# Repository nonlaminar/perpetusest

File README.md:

# perpetusest
For the wandering writer, seeking a keyboard and and space

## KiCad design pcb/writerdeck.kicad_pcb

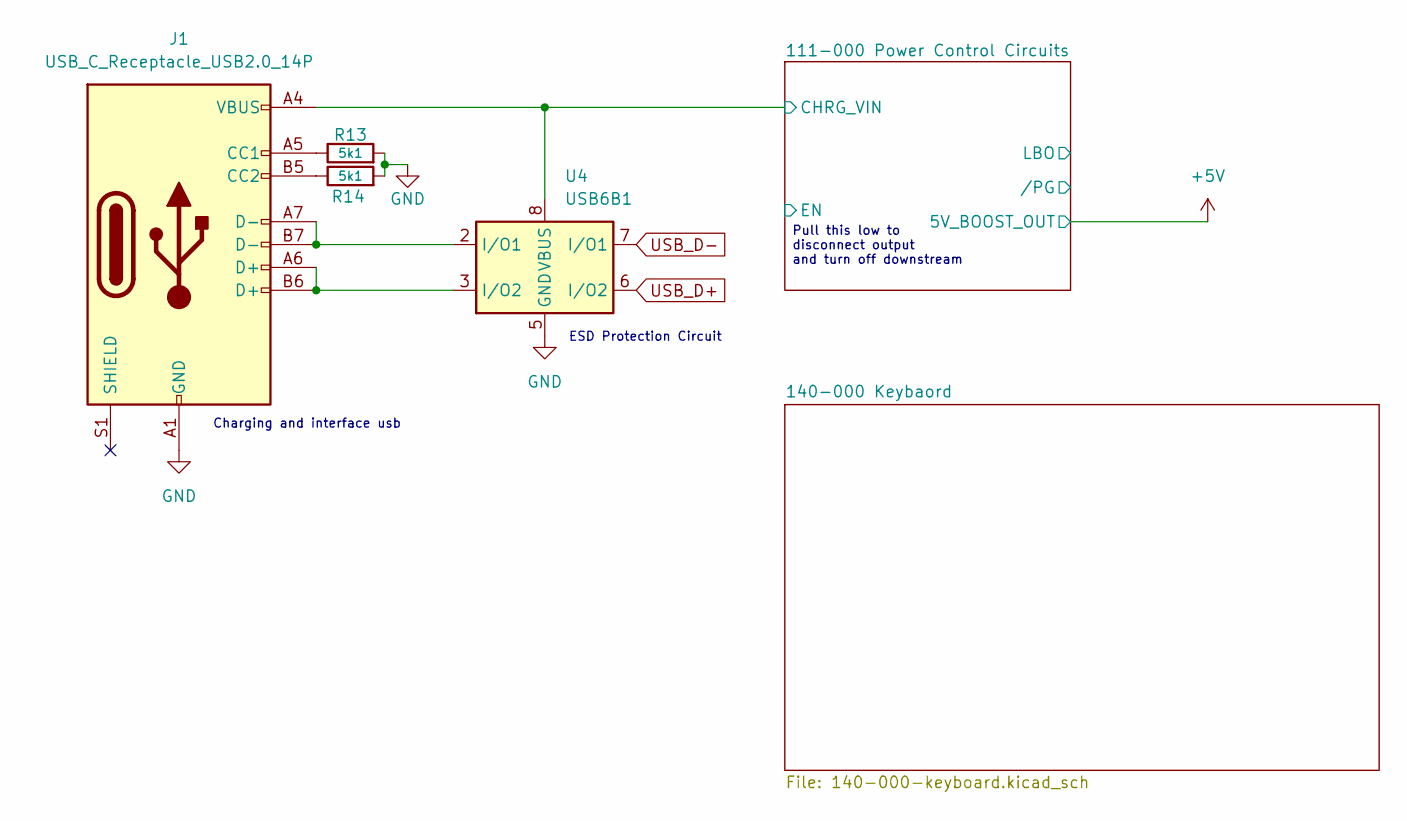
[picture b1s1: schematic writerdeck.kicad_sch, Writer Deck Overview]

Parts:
J1: USB_C_Receptacle_USB2.0_14P
R13, R14: 5k1; R_0402_1005Metric
U4: USB6B1; SOIC-8_3.9x4.9mm_P1.27mm

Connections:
/111-000 Power Control Circuits/CHRG_VIN: J1.A4 (VBUS), J1.A9 (VBUS), J1.B4 (VBUS), J1.B9 (VBUS), U4.1 (VBUS), U4.8 (VBUS); also elsewhere on the board
GND: J1.A1 (GND), J1.A12 (GND), J1.B1 (GND), J1.B12 (GND), R13.2, R14.2, U4.4 (GND), U4.5 (GND); also elsewhere on the board
unnamed: J1.A5 (CC1), R13.1
unnamed: J1.B5 (CC2), R14.1
unnamed: J1.A6 (D+), J1.B6 (D+), U4.3 (I/O2)
unnamed: J1.A7 (D-), J1.B7 (D-), U4.2 (I/O1)
USB_D+: U4.6 (I/O2)
USB_D-: U4.7 (I/O1)

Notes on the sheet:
Charging and interface usb
ESD Protection Circuit
Pull this low to disconnect output and turn off downstream

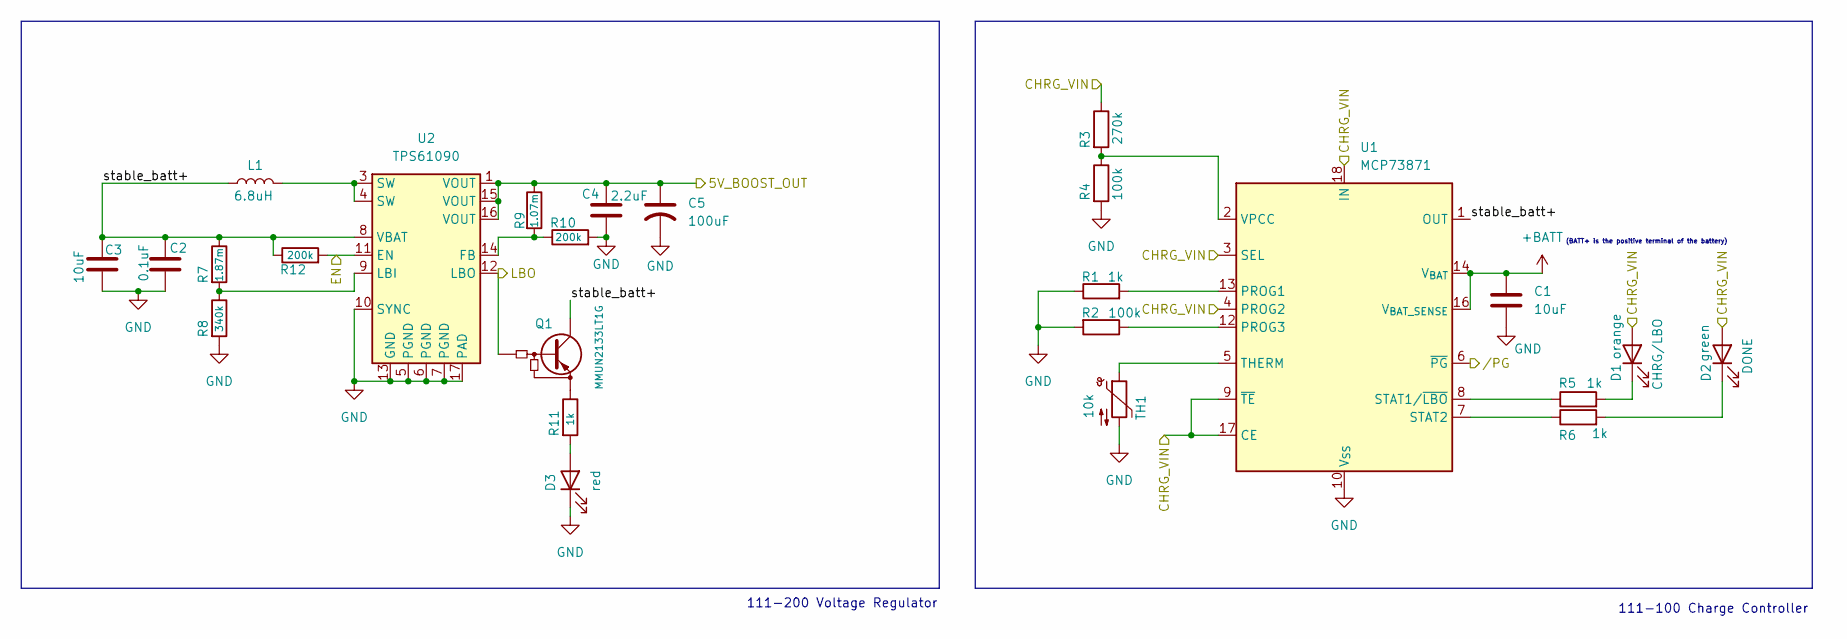
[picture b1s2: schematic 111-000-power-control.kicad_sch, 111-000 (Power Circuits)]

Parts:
C1, C3: 10uF; C_0402_1005Metric
C2: 0.1uF; C_0402_1005Metric
C4: 2.2uF; C_0402_1005Metric
C5: 100uF; C_0402_1005Metric
D1: orange
D2: green
D3: red
L1: 6.8uH
Q1: MMUN2133LT1G
R1, R5, R6, R11: 1k; R_0402_1005Metric
R2, R4: 100k; R_0402_1005Metric
R3: 270k; R_0402_1005Metric
R7: 1.87m; R_0402_1005Metric
R8: 340k; R_0402_1005Metric
R9: 1.07m; R_0402_1005Metric
R10, R12: 200k; R_0402_1005Metric
TH1: 10k; R_0402_1005Metric
U1: MCP73871; QFN-20-1EP_4x4mm_P0.5mm_EP2.5x2.5mm
U2: TPS61090; Texas_RSA_VQFN-16-1EP_4x4mm_P0.65mm_EP2.7x2.7mm_ThermalVias

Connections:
+5V: C4.1, C5.1, R9.1, U2.1 (VOUT), U2.15 (VOUT), U2.16 (VOUT); also elsewhere on the board
+BATT: C1.1, U1.14 (V_{BAT}), U1.15 (V_{BAT}), U1.16 (V_{BAT_SENSE})
/111-000 Power Control Circuits/CHRG_VIN: D1.2 (A), D2.2 (A), R3.1, U1.3 (SEL), U1.4 (PROG2), U1.9 (~TE), U1.17 (CE), U1.18 (IN), U1.19 (IN); also elsewhere on the board
/111-000 Power Control Circuits/EN: R12.2, U2.11 (EN)
/111-000 Power Control Circuits/LBO: Q1.B, U2.12 (LBO)
/111-000 Power Control Circuits/stable_batt+: C2.1, C3.1, L1.1, Q1.C, R7.1, R12.1, U1.1 (OUT), U1.20 (OUT), U2.8 (VBAT)
/111-000 Power Control Circuits//PG: U1.6 (~PG)
GND: C1.2, C2.2, C3.2, C4.2, C5.2, D3.1 (K), R1.1, R2.2, R4.2, R8.2, R10.2, TH1.2, U1.10 (V_{SS}), U1.11 (V_{SS}), U1.21 (V_{SS}), U2.5 (PGND), U2.6 (PGND), U2.7 (PGND), U2.10 (SYNC), U2.13 (GND), U2.17 (PAD); also elsewhere on the board
unnamed: D1.1 (K), R5.2
unnamed: D2.1 (K), R6.2
unnamed: D3.2 (A), R11.2
unnamed: L1.2, U2.3 (SW), U2.4 (SW)
unnamed: Q1.E, R11.1
unnamed: R1.2, U1.13 (PROG1)
unnamed: R2.1, U1.12 (PROG3)
unnamed: R5.1, U1.8 (STAT1/~LBO)
unnamed: R6.1, U1.7 (STAT2)
unnamed: TH1.1, U1.5 (THERM)
unnamed: R3.2, R4.1, U1.2 (VPCC)
unnamed: R9.2, R10.1, U2.14 (FB)
unnamed: R7.2, R8.1, U2.9 (LBI)

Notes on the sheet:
(BATT+ is the positive terminal of the battery)
111-100 Charge Controller
111-200 Voltage Regulator

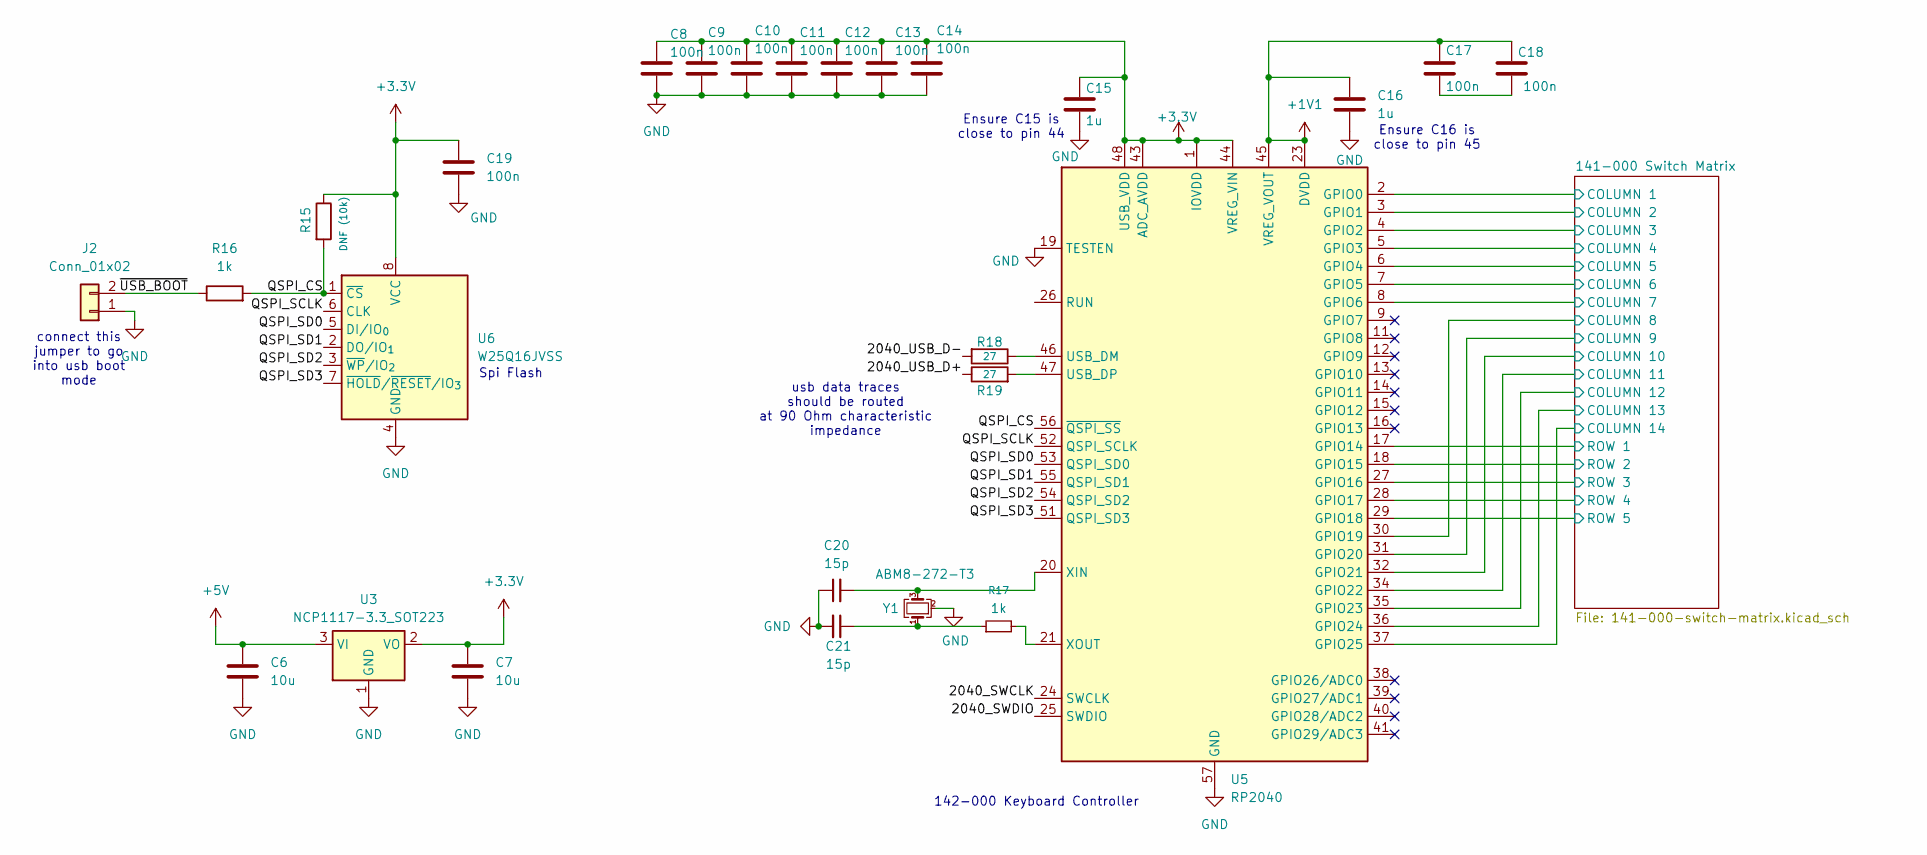
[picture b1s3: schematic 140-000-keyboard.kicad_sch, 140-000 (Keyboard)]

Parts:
C6, C7: 10u; C_0402_1005Metric
C8, C9, C10, C11, C12, C13, C14, C17, C18, C19: 100n; C_0402_1005Metric
C15, C16: 1u; C_0402_1005Metric
C20, C21: 15p; C_0402_1005Metric
J2: Conn_01x02
R15: DNF (10k); R_0402_1005Metric
R16, R17: 1k; R_0402_1005Metric
R18, R19: 27; R_0402_1005Metric
U3: NCP1117-3.3_SOT223; SOT-223-3_TabPin2
U5: RP2040; QFN-56-1EP_7x7mm_P0.4mm_EP3.2x3.2mm
U6: W25Q16JVSS; SOIC-8_5.3x5.3mm_P1.27mm
Y1: ABM8-272-T3; ABM8-272-T3_ABR

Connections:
+1V1: C16.1, C17.1, C18.1, U5.23 (DVDD), U5.45 (VREG_VOUT), U5.50 (DVDD)
+3.3V: C7.1, C8.1, C9.1, C10.1, C11.1, C12.1, C13.1, C14.1, C15.1, C19.1, R15.1, U3.2 (VO), U5.1 (IOVDD), U5.10 (IOVDD), U5.22 (IOVDD), U5.33 (IOVDD), U5.42 (IOVDD), U5.43 (ADC_AVDD), U5.44 (VREG_VIN), U5.48 (USB_VDD), U5.49 (IOVDD), U6.8 (VCC)
+5V: C6.1, U3.3 (VI); also elsewhere on the board
/140-000 Keybaord/141-000 Switch Matrix/COLUMN 1: U5.2 (GPIO0); also elsewhere on the board
/140-000 Keybaord/141-000 Switch Matrix/COLUMN 2: U5.3 (GPIO1); also elsewhere on the board
/140-000 Keybaord/141-000 Switch Matrix/COLUMN 3: U5.4 (GPIO2); also elsewhere on the board
/140-000 Keybaord/141-000 Switch Matrix/COLUMN 4: U5.5 (GPIO3); also elsewhere on the board
/140-000 Keybaord/141-000 Switch Matrix/COLUMN 5: U5.6 (GPIO4); also elsewhere on the board
/140-000 Keybaord/141-000 Switch Matrix/COLUMN 6: U5.7 (GPIO5); also elsewhere on the board
/140-000 Keybaord/141-000 Switch Matrix/COLUMN 7: U5.8 (GPIO6); also elsewhere on the board
/140-000 Keybaord/141-000 Switch Matrix/COLUMN 8: U5.30 (GPIO19); also elsewhere on the board
/140-000 Keybaord/141-000 Switch Matrix/COLUMN 9: U5.31 (GPIO20); also elsewhere on the board
/140-000 Keybaord/141-000 Switch Matrix/COLUMN 10: U5.32 (GPIO21); also elsewhere on the board
/140-000 Keybaord/141-000 Switch Matrix/COLUMN 11: U5.34 (GPIO22); also elsewhere on the board
/140-000 Keybaord/141-000 Switch Matrix/COLUMN 12: U5.35 (GPIO23); also elsewhere on the board
/140-000 Keybaord/141-000 Switch Matrix/COLUMN 13: U5.36 (GPIO24); also elsewhere on the board
/140-000 Keybaord/141-000 Switch Matrix/COLUMN 14: U5.37 (GPIO25); also elsewhere on the board
/140-000 Keybaord/141-000 Switch Matrix/ROW 1: U5.17 (GPIO14); also elsewhere on the board
/140-000 Keybaord/141-000 Switch Matrix/ROW 2: U5.18 (GPIO15); also elsewhere on the board
/140-000 Keybaord/141-000 Switch Matrix/ROW 3: U5.27 (GPIO16); also elsewhere on the board
/140-000 Keybaord/141-000 Switch Matrix/ROW 4: U5.28 (GPIO17); also elsewhere on the board
/140-000 Keybaord/141-000 Switch Matrix/ROW 5: U5.29 (GPIO18); also elsewhere on the board
/140-000 Keybaord/2040_SWCLK: U5.24 (SWCLK)
/140-000 Keybaord/2040_SWDIO: U5.25 (SWDIO)
/140-000 Keybaord/2040_USB_D+: R19.1
/140-000 Keybaord/2040_USB_D-: R18.2
/140-000 Keybaord/QSPI_CS: R15.2, R16.2, U5.56 (~QSPI_SS), U6.1 (~CS)
/140-000 Keybaord/QSPI_SCLK: U5.52 (QSPI_SCLK), U6.6 (CLK)
/140-000 Keybaord/QSPI_SD0: U5.53 (QSPI_SD0), U6.5 (DI/IO_{0})
/140-000 Keybaord/QSPI_SD1: U5.55 (QSPI_SD1), U6.2 (DO/IO_{1})
/140-000 Keybaord/QSPI_SD2: U5.54 (QSPI_SD2), U6.3 (~WP/IO_{2})
/140-000 Keybaord/QSPI_SD3: U5.51 (QSPI_SD3), U6.7 (~HOLD/~RESET/IO_{3})
/140-000 Keybaord/~USB_BOOT: J2.2, R16.1
GND: C6.2, C7.2, C8.2, C9.2, C10.2, C11.2, C12.2, C13.2, C14.2, C15.2, C16.2, C19.2, C20.1, C21.2, J2.1, U3.1 (GND), U5.19 (TESTEN), U5.57 (GND), U6.4 (GND), Y1.2 (G), Y1.4 (G); also elsewhere on the board
unnamed: C17.2, C18.2
unnamed: C21.1, R17.1, Y1.1
unnamed: R18.1, U5.46 (USB_DM)
unnamed: R19.2, U5.47 (USB_DP)
unnamed: C20.2, U5.20 (XIN), Y1.3
unnamed: R17.2, U5.21 (XOUT)

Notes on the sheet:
usb data traces should be routed at 90 Ohm characteristic impedance
Spi Flash
Ensure C16 is close to pin 45
Ensure C15 is close to pin 44
142-000 Keyboard Controller
connect this jumper to go into usb boot mode

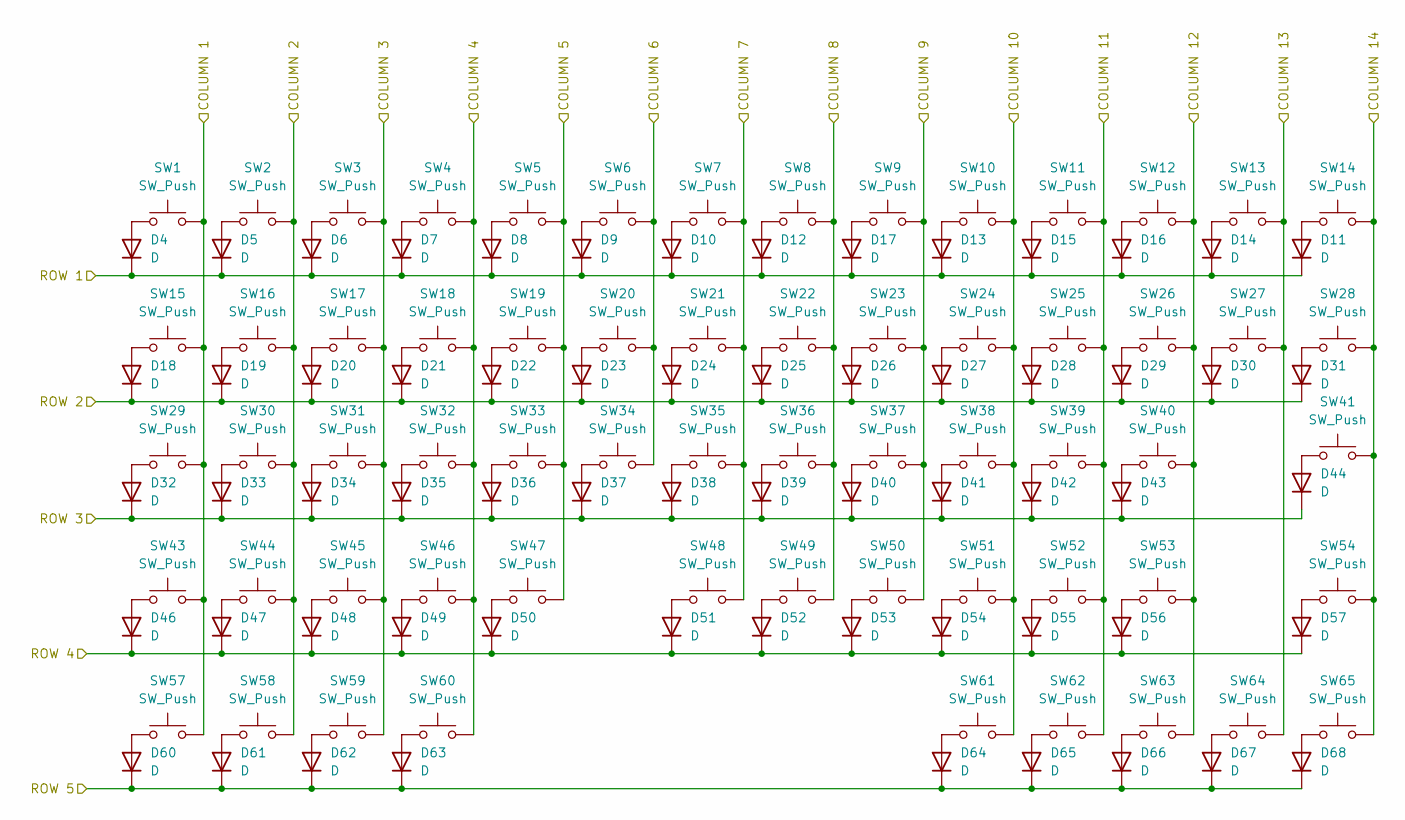
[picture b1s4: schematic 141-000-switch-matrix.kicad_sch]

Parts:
D4, D5, D6, D7, D8, D9, D10, D11, D12, D13, D14, D15, D16, D17, D18, D19, D20, D21, D22, D23, D24, D25, D26, D27, D28, D29, D30, D31, D32, D33, D34, D35, D36, D37, D38, D39, D40, D41, D42, D43, D44, D46, D47, D48, D49, D50, D51, D52, D53, D54, D55, D56, D57, D60, D61, D62, D63, D64, D65, D66, D67, D68: D; D_0402_1005Metric
SW1, SW2, SW3, SW4, SW5, SW6, SW7, SW8, SW9, SW10, SW11, SW12, SW13, SW16, SW17, SW18, SW19, SW20, SW21, SW22, SW23, SW24, SW25, SW26, SW27, SW30, SW31, SW32, SW33, SW34, SW35, SW36, SW37, SW38, SW39, SW40, SW44, SW45, SW46, SW47, SW48, SW49, SW50, SW51, SW52, SW53: SW_Push; SW_Kailh_Choc_V2_1.00u
SW14: SW_Push; SW_Kailh_Choc_V2_2.00u
SW15, SW28, SW65: SW_Push; SW_Kailh_Choc_V2_1.50u
SW29: SW_Push; SW_Kailh_Choc_V2_1.75u
SW41, SW43: SW_Push; SW_Kailh_Choc_V2_2.25u
SW54: SW_Push; SW_Kailh_Choc_V2_2.75u
SW57, SW58, SW59, SW62, SW63, SW64: SW_Push; SW_Kailh_Choc_V2_1.25u
SW60, SW61: SW_Push; SW_Kailh_Choc_V2_3.00u

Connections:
/140-000 Keybaord/141-000 Switch Matrix/COLUMN 1: SW1.2, SW15.2, SW29.2, SW43.2, SW57.2; also elsewhere on the board
/140-000 Keybaord/141-000 Switch Matrix/COLUMN 2: SW2.2, SW16.2, SW30.2, SW44.2, SW58.2; also elsewhere on the board
/140-000 Keybaord/141-000 Switch Matrix/COLUMN 3: SW3.2, SW17.2, SW31.2, SW45.2, SW59.2; also elsewhere on the board
/140-000 Keybaord/141-000 Switch Matrix/COLUMN 4: SW4.2, SW18.2, SW32.2, SW46.2, SW60.2; also elsewhere on the board
/140-000 Keybaord/141-000 Switch Matrix/COLUMN 5: SW5.2, SW19.2, SW33.2, SW47.2; also elsewhere on the board
/140-000 Keybaord/141-000 Switch Matrix/COLUMN 6: SW6.2, SW20.2, SW34.2; also elsewhere on the board
/140-000 Keybaord/141-000 Switch Matrix/COLUMN 7: SW7.2, SW21.2, SW35.2, SW48.2; also elsewhere on the board
/140-000 Keybaord/141-000 Switch Matrix/COLUMN 8: SW8.2, SW22.2, SW36.2, SW49.2; also elsewhere on the board
/140-000 Keybaord/141-000 Switch Matrix/COLUMN 9: SW9.2, SW23.2, SW37.2, SW50.2; also elsewhere on the board
/140-000 Keybaord/141-000 Switch Matrix/COLUMN 10: SW10.2, SW24.2, SW38.2, SW51.2, SW61.2; also elsewhere on the board
/140-000 Keybaord/141-000 Switch Matrix/COLUMN 11: SW11.2, SW25.2, SW39.2, SW52.2, SW62.2; also elsewhere on the board
/140-000 Keybaord/141-000 Switch Matrix/COLUMN 12: SW12.2, SW26.2, SW40.2, SW53.2, SW63.2; also elsewhere on the board
/140-000 Keybaord/141-000 Switch Matrix/COLUMN 13: SW13.2, SW27.2, SW64.2; also elsewhere on the board
/140-000 Keybaord/141-000 Switch Matrix/COLUMN 14: SW14.2, SW28.2, SW41.2, SW54.2, SW65.2; also elsewhere on the board
/140-000 Keybaord/141-000 Switch Matrix/ROW 1: D4.1 (K), D5.1 (K), D6.1 (K), D7.1 (K), D8.1 (K), D9.1 (K), D10.1 (K), D11.1 (K), D12.1 (K), D13.1 (K), D14.1 (K), D15.1 (K), D16.1 (K), D17.1 (K); also elsewhere on the board
/140-000 Keybaord/141-000 Switch Matrix/ROW 2: D18.1 (K), D19.1 (K), D20.1 (K), D21.1 (K), D22.1 (K), D23.1 (K), D24.1 (K), D25.1 (K), D26.1 (K), D27.1 (K), D28.1 (K), D29.1 (K), D30.1 (K), D31.1 (K); also elsewhere on the board
/140-000 Keybaord/141-000 Switch Matrix/ROW 3: D32.1 (K), D33.1 (K), D34.1 (K), D35.1 (K), D36.1 (K), D37.1 (K), D38.1 (K), D39.1 (K), D40.1 (K), D41.1 (K), D42.1 (K), D43.1 (K), D44.1 (K); also elsewhere on the board
/140-000 Keybaord/141-000 Switch Matrix/ROW 4: D46.1 (K), D47.1 (K), D48.1 (K), D49.1 (K), D50.1 (K), D51.1 (K), D52.1 (K), D53.1 (K), D54.1 (K), D55.1 (K), D56.1 (K), D57.1 (K); also elsewhere on the board
/140-000 Keybaord/141-000 Switch Matrix/ROW 5: D60.1 (K), D61.1 (K), D62.1 (K), D63.1 (K), D64.1 (K), D65.1 (K), D66.1 (K), D67.1 (K), D68.1 (K); also elsewhere on the board
unnamed: D4.2 (A), SW1.1
unnamed: D5.2 (A), SW2.1
unnamed: D6.2 (A), SW3.1
unnamed: D7.2 (A), SW4.1
unnamed: D8.2 (A), SW5.1
unnamed: D9.2 (A), SW6.1
unnamed: D10.2 (A), SW7.1
unnamed: D11.2 (A), SW14.1
unnamed: D12.2 (A), SW8.1
unnamed: D13.2 (A), SW10.1
unnamed: D14.2 (A), SW13.1
unnamed: D15.2 (A), SW11.1
unnamed: D16.2 (A), SW12.1
unnamed: D17.2 (A), SW9.1
unnamed: D18.2 (A), SW15.1
unnamed: D19.2 (A), SW16.1
unnamed: D20.2 (A), SW17.1
unnamed: D21.2 (A), SW18.1
unnamed: D22.2 (A), SW19.1
unnamed: D23.2 (A), SW20.1
unnamed: D24.2 (A), SW21.1
unnamed: D25.2 (A), SW22.1
unnamed: D26.2 (A), SW23.1
unnamed: D27.2 (A), SW24.1
unnamed: D28.2 (A), SW25.1
unnamed: D29.2 (A), SW26.1
unnamed: D30.2 (A), SW27.1
unnamed: D31.2 (A), SW28.1
unnamed: D32.2 (A), SW29.1
unnamed: D33.2 (A), SW30.1
unnamed: D34.2 (A), SW31.1
unnamed: D35.2 (A), SW32.1
unnamed: D36.2 (A), SW33.1
unnamed: D37.2 (A), SW34.1
unnamed: D38.2 (A), SW35.1
unnamed: D39.2 (A), SW36.1
unnamed: D40.2 (A), SW37.1
unnamed: D41.2 (A), SW38.1
unnamed: D42.2 (A), SW39.1
unnamed: D43.2 (A), SW40.1
unnamed: D44.2 (A), SW41.1
unnamed: D46.2 (A), SW43.1
unnamed: D47.2 (A), SW44.1
unnamed: D48.2 (A), SW45.1
unnamed: D49.2 (A), SW46.1
unnamed: D50.2 (A), SW47.1
unnamed: D51.2 (A), SW48.1
unnamed: D52.2 (A), SW49.1
unnamed: D53.2 (A), SW50.1
unnamed: D54.2 (A), SW51.1
unnamed: D55.2 (A), SW52.1
unnamed: D56.2 (A), SW53.1
unnamed: D57.2 (A), SW54.1
unnamed: D60.2 (A), SW57.1
unnamed: D61.2 (A), SW58.1
unnamed: D62.2 (A), SW59.1
unnamed: D63.2 (A), SW60.1
unnamed: D64.2 (A), SW61.1
unnamed: D65.2 (A), SW62.1
unnamed: D66.2 (A), SW63.1
unnamed: D67.2 (A), SW64.1
unnamed: D68.2 (A), SW65.1

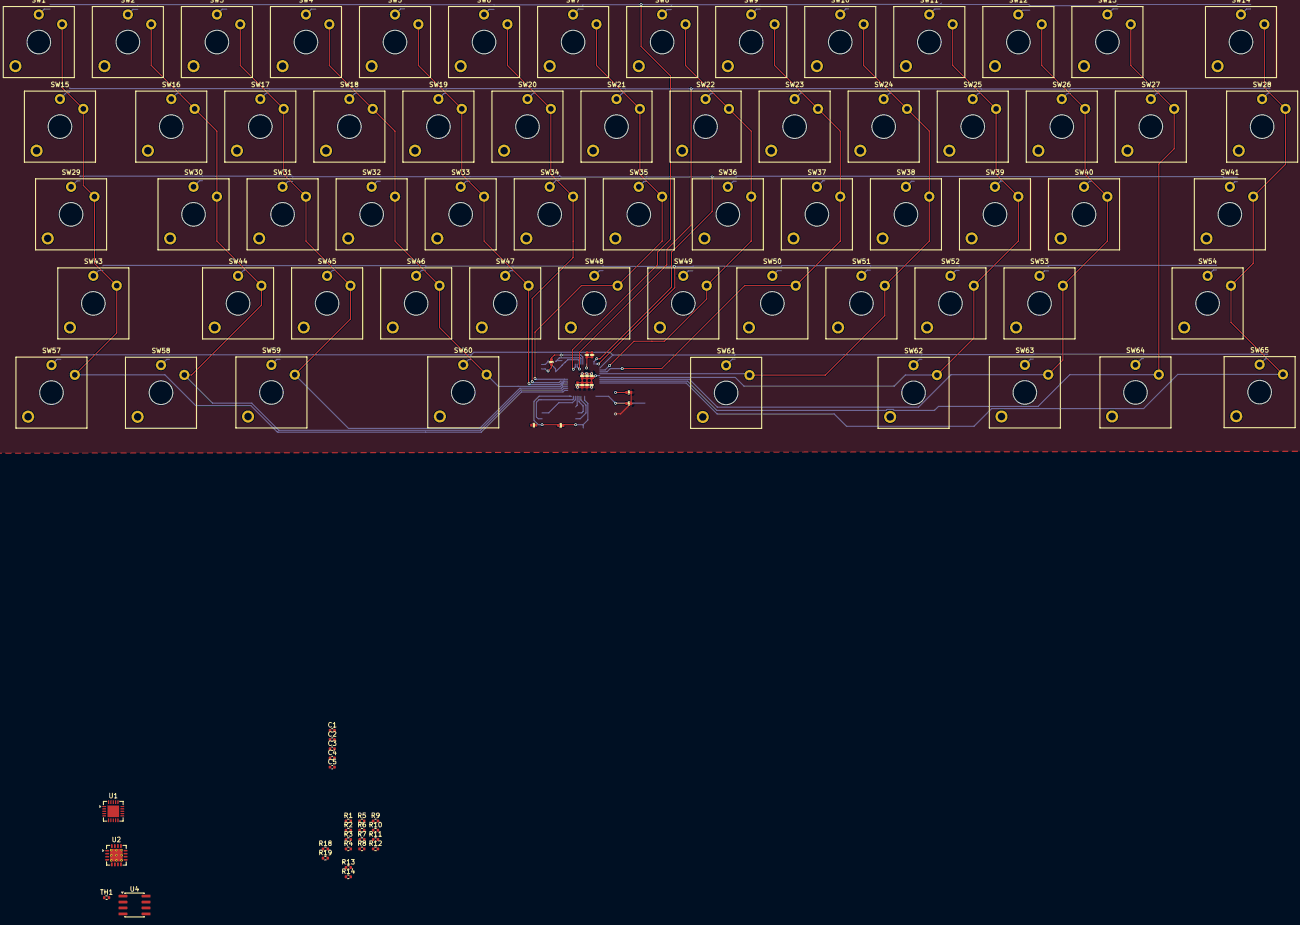
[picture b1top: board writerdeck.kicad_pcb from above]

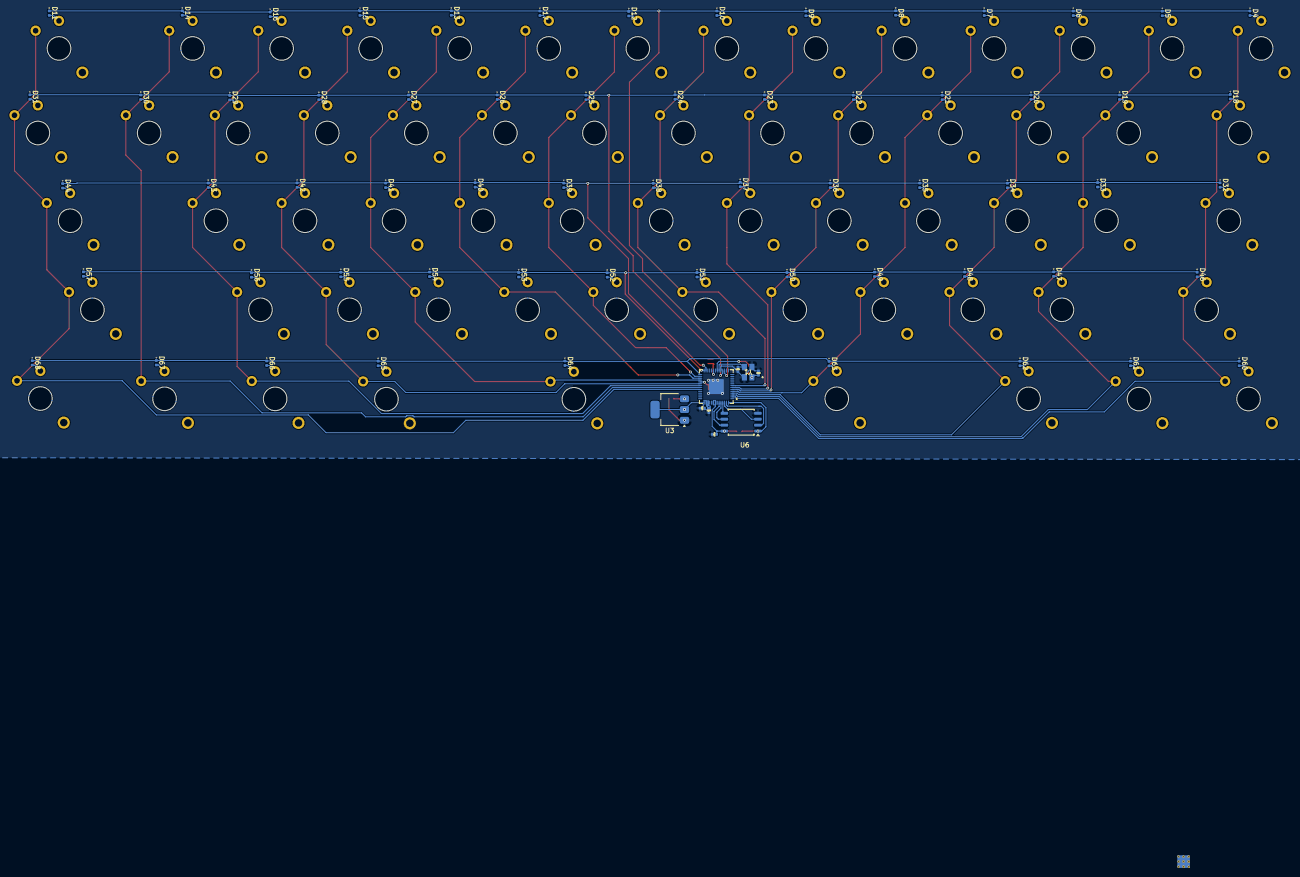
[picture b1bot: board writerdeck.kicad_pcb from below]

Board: 2 copper layers, 172 parts (71 on the bottom side), 110 nets.

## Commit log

2026-04-08 add pcb
2026-04-08 add keyboard
2026-04-08 remove uneeded files
2026-04-08 add datasheets
2026-04-08 add rp2040 datasheet, and add rp2040 to keyboard unconnected
2026-04-11 add epaper spec
2026-04-11 add epaper W/ LUT spec
2026-04-11 add start of epaper driver files
2026-05-17 add git ignore, and new sheets etc
2026-05-22 major keyboard components completed
